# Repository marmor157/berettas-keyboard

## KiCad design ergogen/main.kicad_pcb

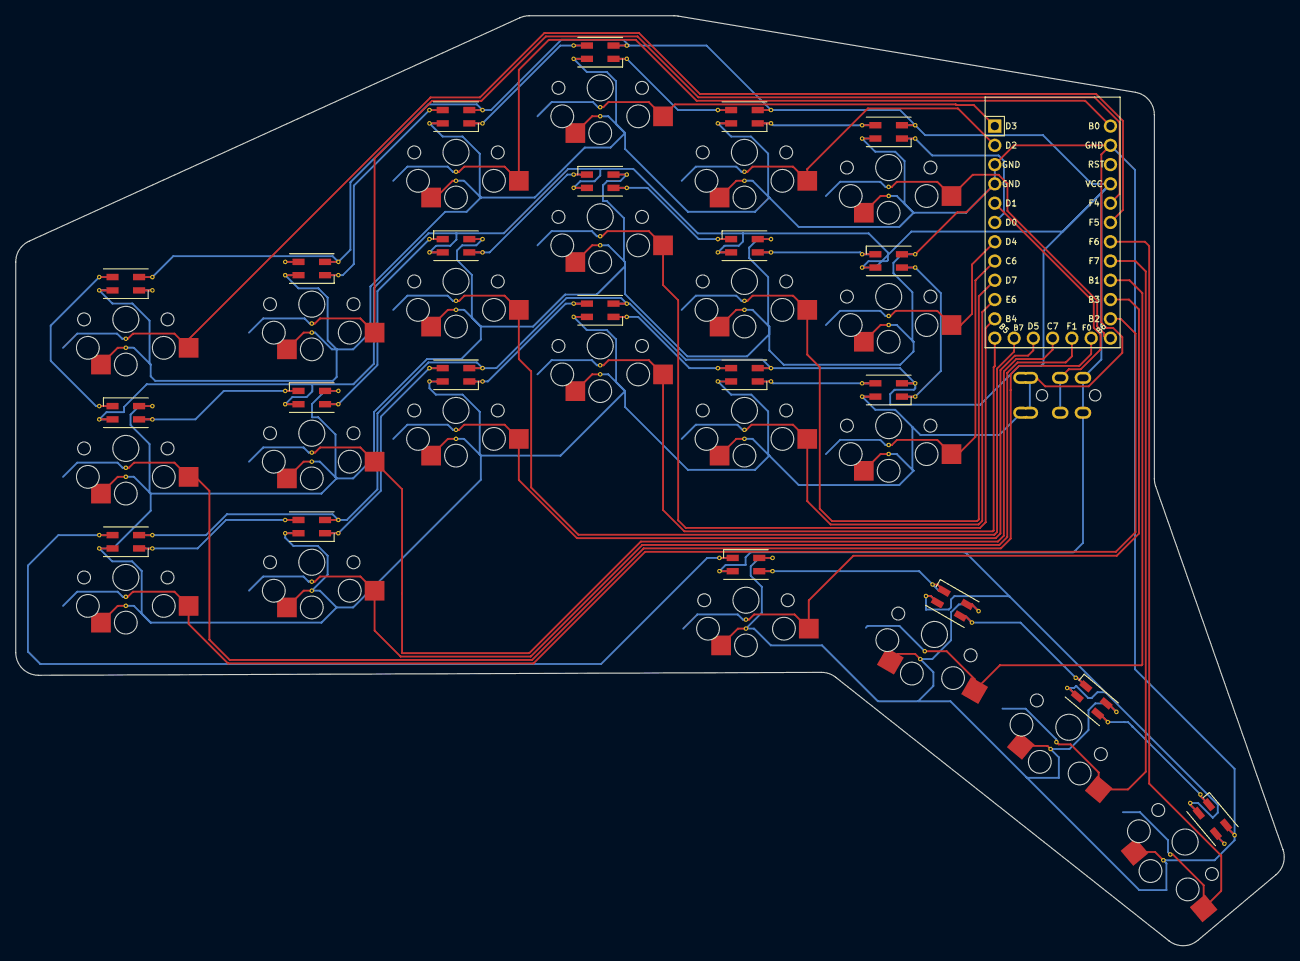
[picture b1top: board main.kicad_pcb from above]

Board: 2 copper layers, 167.1 x 122.5 mm, 46 parts (0 on the bottom side), 26 nets.

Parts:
MCU1: Elite-C
S1, S2, S3, S4, S5, S6, S7, S8, S9, S10, S11, S12, S13, S14, S15, S16, S17, S18, S19, S20, S21, S22: PG1350
TRRS1: TRRS-PJ-320A-dual
_3, _6, _9, _12, _15, _18, _21, _24, _27, _30, _33, _36, _39, _42, _45, _48, _51, _54, _57, _60, _63, _66: SK6812-Mini-3535

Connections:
B0: MCU1.24, S9.2
B1: MCU1.16, S20.2
B2: MCU1.14, S1.2
B3: MCU1.15, S19.2
B4: MCU1.11, S11.2
B5: MCU1.12, S10.2
B6: MCU1.13, S18.2
B7: MCU1.25, S8.2
C6: MCU1.8, S16.2
C7: MCU1.27, S5.2
D0: MCU1.6, _3.1, _3.3, _6.1, _6.3, _9.1, _9.3, _12.1, _12.3, _15.1, _15.3, _18.1, _18.3, _21.1, _21.3, _24.1, _24.3, _27.1, _27.3, _30.1, _30.3, _33.1, _33.3, _36.1, _36.3, _39.1, _39.3, _42.1, _42.3, _45.1, _45.3, _48.1, _48.3, _51.1, _51.3, _54.1, _54.3, _57.1, _57.3, _60.1, _60.3, _63.1, _63.3, _66.1, _66.3
D1: MCU1.5, TRRS1.3
D2: MCU1.2, S15.2
D3: MCU1.1, S12.2
D4: MCU1.7, S17.2
D5: MCU1.26, S7.2
D7: MCU1.9, S14.2
E6: MCU1.10, S13.2
F0: MCU1.29, S2.2
F1: MCU1.28, S4.2
F4: MCU1.20, S6.2
F5: MCU1.19, S3.2
F6: MCU1.18, S22.2
F7: MCU1.17, S21.2
GND: MCU1.3, MCU1.4, MCU1.23, S1.1, S2.1, S3.1, S4.1, S5.1, S6.1, S7.1, S8.1, S9.1, S10.1, S11.1, S12.1, S13.1, S14.1, S15.1, S16.1, S17.1, S18.1, S19.1, S20.1, S21.1, S22.1, TRRS1.1, TRRS1.2, _3.2, _6.2, _9.2, _12.2, _15.2, _18.2, _21.2, _24.2, _27.2, _30.2, _33.2, _36.2, _39.2, _42.2, _45.2, _48.2, _51.2, _54.2, _57.2, _60.2, _63.2, _66.2
VCC: MCU1.21, TRRS1.4, _3.4, _6.4, _9.4, _12.4, _15.4, _18.4, _21.4, _24.4, _27.4, _30.4, _33.4, _36.4, _39.4, _42.4, _45.4, _48.4, _51.4, _54.4, _57.4, _60.4, _63.4, _66.4

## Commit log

2022-05-19 Inital commit
2022-05-19 Add ergpgen yaml and kicad_pcb
2022-05-19 Add QMK files
2022-05-19 Fix TRRS pin in ergogen and kicad
2022-07-24 Basic keymap and try via
2022-09-26 Add mod taps and tap toggle to layers
2023-11-20 Add equals and rbak to second layer
